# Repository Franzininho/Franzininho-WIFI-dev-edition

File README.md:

# Franzininho WiFi Developer Edition

The **Franzininho WiFi Developer Edition** is a development board designed to evaluate **ESP32-S2 modules** (WROOM and WROVER) and to support the development of the next generation of Franzininho boards.

The Franzininho project was created to help people develop skills in electronics and programming through *DIY* (Do-It-Yourself) activities, aligned with the *maker culture* in Brazil.

As there are still few ESP32-S2-based boards available in the Brazilian market, the Franzininho WiFi was developed to serve as a development platform for this SoC, as well as to help evaluate and validate applications.

---

## Features

### ESP32-S2 Module (WROOM or WROVER)
- Xtensa® LX7 32-bit single-core microprocessor, up to 240 MHz  
- 128 KB ROM  
- 320 KB SRAM  
- 16 KB RTC SRAM  
- 2 MB (8 Mbit) PSRAM (WROVER module only)  
- Wi-Fi 802.11 b/g/n  

### Interfaces
- GPIO, SPI, LCD, UART, I2C, I2S  
- Camera interface  
- IR, pulse counter, LED PWM  
- TWAI (compatible with ISO 11898-1)  
- USB 1.1 OTG  
- ADC, DAC  
- Touch sensor  
- Temperature sensor  

### Hardware
- USB Type-A male connector  
- RGB LED (WS2812) (GPIO 18)  
- 40 pins broken out to 2x20 headers (2.54 mm pitch, 36 GPIOs) — breadboard-friendly  
- Reset and DFU (BOOT0) buttons to enter the ROM bootloader (USB serial, no external adapter required)  
- Serial debug pins (TX and RX) for hardware debug console  
- JTAG pads for advanced debugging access  
- 3.3 V power indicator LED  
- 3.3 V voltage regulator  

### Power Supply
- Micro USB port (default power source)  
- 5 V and GND header pins  
- 3V3 and GND header pins  

### Dimensions
- 72 mm x 30 mm  

### Compatibility
- Compatible with [ESP-IDF](https://docs.espressif.com/projects/esp-idf/en/latest/esp32s2/get-started/index.html)  
- Compatible with [CircuitPython](https://circuitpython.org/)  

---

## License

This project is open-source hardware and is released under the **CERN Open Hardware License**.

The Franzininho WiFi board is certified by OSHWA:  
[UID BR000006](https://certification.oshwa.org/br000006.html)

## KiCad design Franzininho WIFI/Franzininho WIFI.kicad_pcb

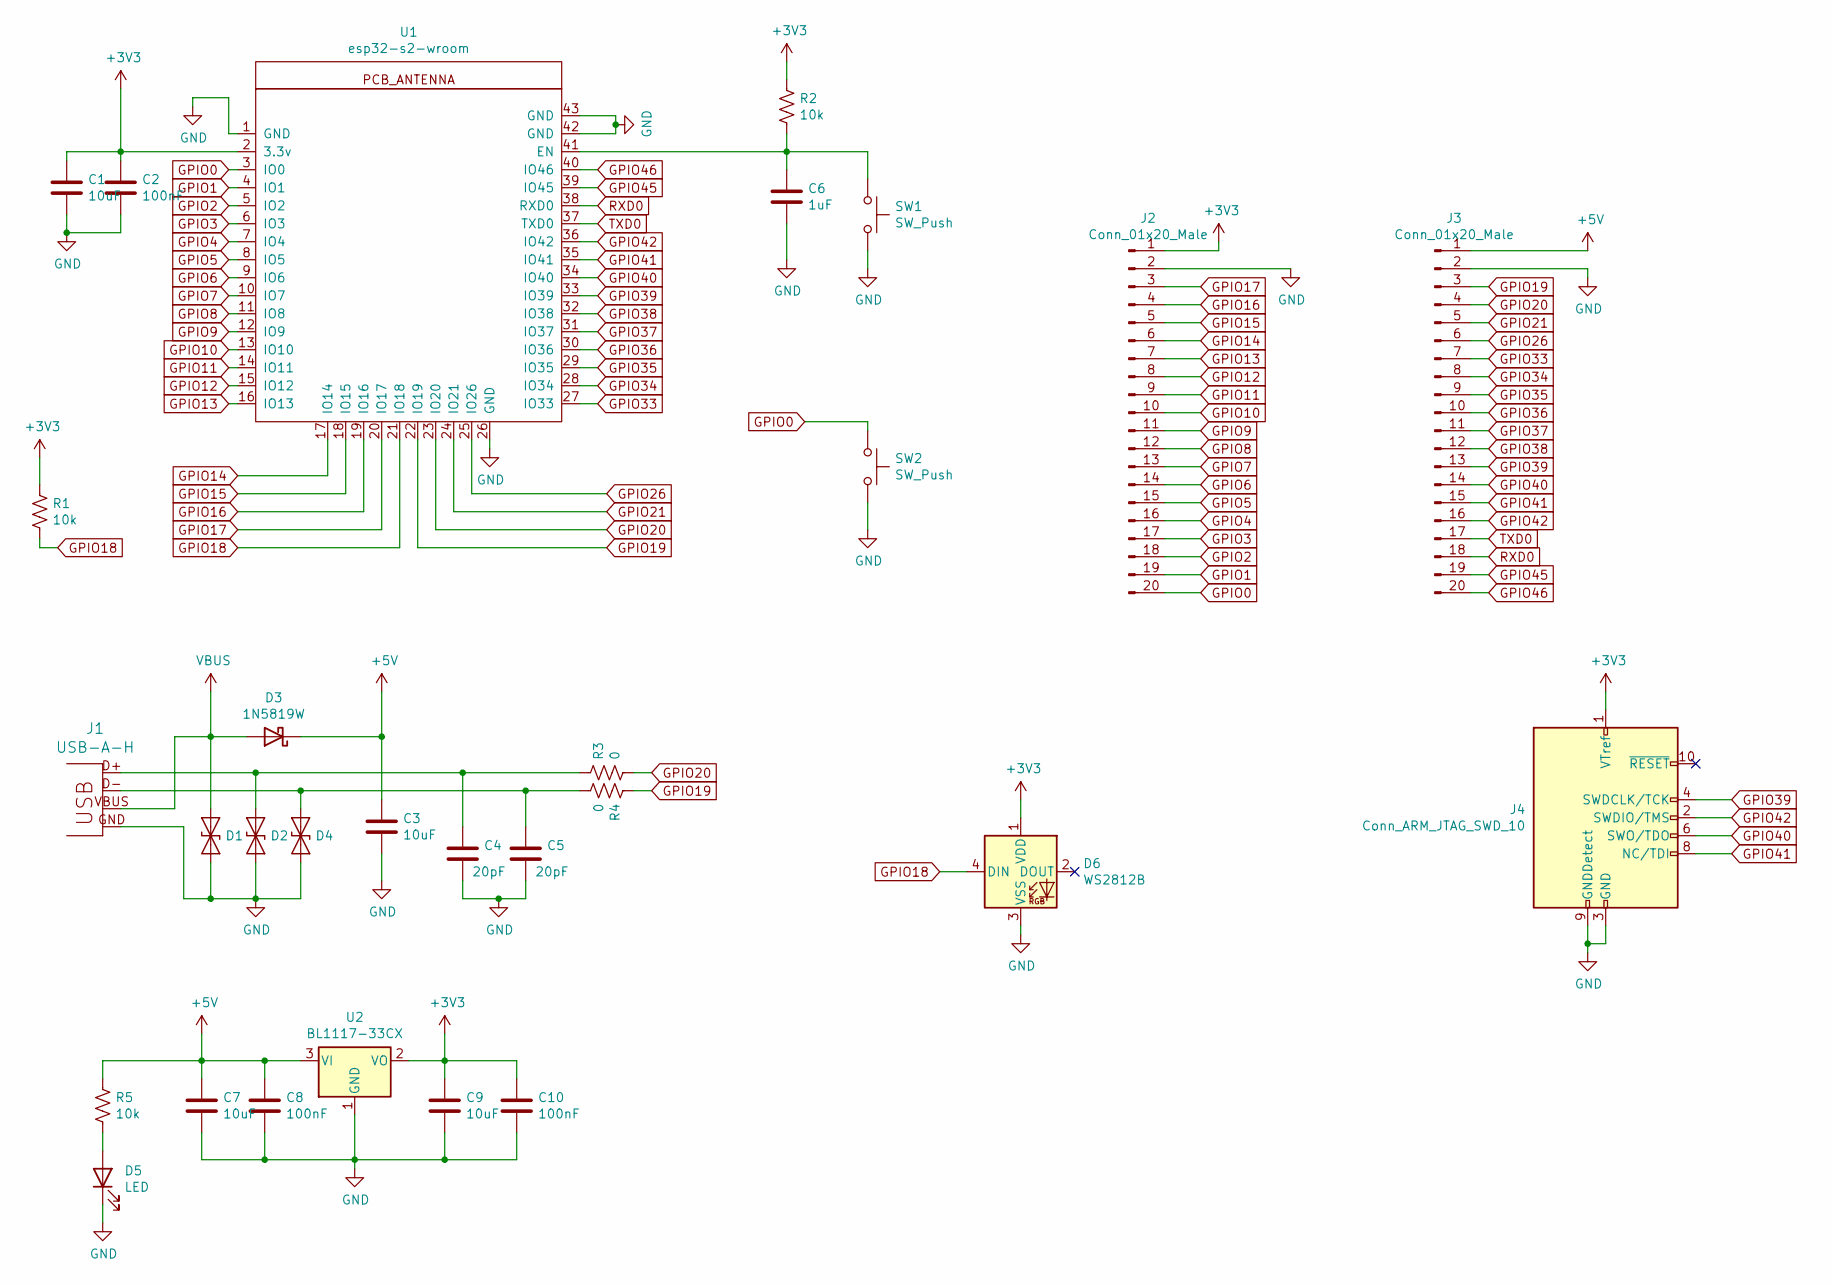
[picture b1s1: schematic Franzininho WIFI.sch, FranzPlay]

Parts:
C1, C3, C7, C9: 10uF; C_0603_1608Metric; LCSC C19702
C2, C8, C10: 100nF; C_0603_1608Metric; LCSC C14663
C4, C5: 20pF; C_0603_1608Metric; LCSC C1648
C6: 1uF; C_0603_1608Metric; LCSC C15849
D1, D2, D4: LESD5D5.0CT1G; D_SOD-523; LCSC C136171
D3: 1N5819W; D_SOD-123F; LCSC C169540
D5: LED; LED_0603_1608Metric; LCSC C2289
D6: WS2812B; LED_WS2812B_PLCC4_5.0x5.0mm_P3.2mm; LCSC C114586
J1: USB-A-H
J2, J3: Conn_01x20_Male; PinSocket_1x20_P2.54mm_Vertical
J4: Conn_ARM_JTAG_SWD_10; PinHeader_2x05_P1.27mm_Vertical_SMD
R1, R2, R5: 10k; R_0603_1608Metric; LCSC C25804
R3, R4: 0; R_0603_1608Metric; LCSC C21189
SW1, SW2: SW_Push; SW_SPST_B3U-1000P
U1: esp32-s2-wroom; esp32-s2-wrooom
U2: BL1117-33CX; SOT-223-3_TabPin2; LCSC C5400

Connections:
+3V3: C1.1, C2.1, C9.1, C10.1, D6.1 (VDD), J2.1, J4.1 (VTref), R1.1, R2.1, U1.2 (3.3v), U2.2 (VO)
+5V: C3.1, C7.1, C8.1, D3.1 (K), J3.1, R5.1, U2.3 (VI)
GND: C1.2, C2.2, C3.2, C4.2, C5.2, C6.2, C7.2, C8.2, C9.2, C10.2, D1.2 (A2), D2.2 (A2), D4.2 (A2), D5.1 (K), D6.3 (VSS), J1.GND, J2.2, J3.2, J4.3 (GND), J4.5 (GND), J4.9 (GNDDetect), SW1.2, SW2.2, U1.1 (GND), U1.26 (GND), U1.42 (GND), U1.43 (GND), U2.1 (GND)
GPIO0: J2.20, SW2.1, U1.3 (IO0)
GPIO1: J2.19, U1.4 (IO1)
GPIO2: J2.18, U1.5 (IO2)
GPIO3: J2.17, U1.6 (IO3)
GPIO4: J2.16, U1.7 (IO4)
GPIO5: J2.15, U1.8 (IO5)
GPIO6: J2.14, U1.9 (IO6)
GPIO7: J2.13, U1.10 (IO7)
GPIO8: J2.12, U1.11 (IO8)
GPIO9: J2.11, U1.12 (IO9)
GPIO10: J2.10, U1.13 (IO10)
GPIO11: J2.9, U1.14 (IO11)
GPIO12: J2.8, U1.15 (IO12)
GPIO13: J2.7, U1.16 (IO13)
GPIO14: J2.6, U1.17 (IO14)
GPIO15: J2.5, U1.18 (IO15)
GPIO16: J2.4, U1.19 (IO16)
GPIO17: J2.3, U1.20 (IO17)
GPIO18: D6.4 (DIN), R1.2, U1.21 (IO18)
GPIO19: J3.3, R4.1, U1.22 (IO19)
GPIO20: J3.4, R3.2, U1.23 (IO20)
GPIO21: J3.5, U1.24 (IO21)
GPIO26: J3.6, U1.25 (IO26)
GPIO33: J3.7, U1.27 (IO33)
GPIO34: J3.8, U1.28 (IO34)
GPIO35: J3.9, U1.29 (IO35)
GPIO36: J3.10, U1.30 (IO36)
GPIO37: J3.11, U1.31 (IO37)
GPIO38: J3.12, U1.32 (IO38)
GPIO39: J3.13, J4.4 (SWDCLK/TCK), U1.33 (IO39)
GPIO40: J3.14, J4.6 (SWO/TDO), U1.34 (IO40)
GPIO41: J3.15, J4.8 (NC/TDI), U1.35 (IO41)
GPIO42: J3.16, J4.2 (SWDIO/TMS), U1.36 (IO42)
GPIO45: J3.19, U1.39 (IO45)
GPIO46: J3.20, U1.40 (IO46)
unnamed: C4.1, D2.1 (A1), J1.D+, R3.1
unnamed: C5.1, D4.1 (A1), J1.D-, R4.2
unnamed: C6.1, R2.2, SW1.1, U1.41 (EN)
unnamed: D5.2 (A), R5.2
RXD0: J3.18, U1.38 (RXD0)
TXD0: J3.17, U1.37 (TXD0)
VBUS: D1.1 (A1), D3.2 (A), J1.VBUS

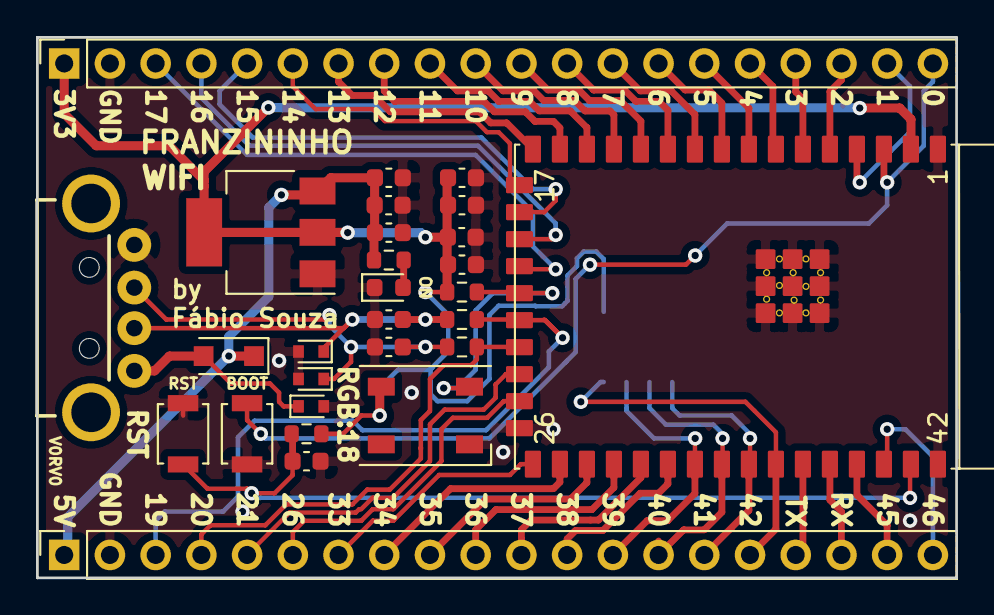
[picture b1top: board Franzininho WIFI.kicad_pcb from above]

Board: 2 copper layers, 51.1 x 30.0 mm, 29 parts (0 on the bottom side), 45 nets.

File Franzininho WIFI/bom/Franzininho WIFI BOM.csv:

Reference, Value, Footprint, Datasheet, LCSC, PN
"U1","esp32-s2-wroom","esp32-s2:esp32-s2-wrooom",""
"D1","LESD5D5.0CT1G","Diode_SMD:D_SOD-523","https://datasheet.lcsc.com/szlcsc/Leshan-Radio-LESD5Z5-0T1G_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","C136171","LESD5Z5.0T1G"
"D2","LESD5D5.0CT1G","Diode_SMD:D_SOD-523","https://datasheet.lcsc.com/szlcsc/Leshan-Radio-LESD5Z5-0T1G_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","C136171","LESD5Z5.0T1G"
"D4","LESD5D5.0CT1G","Diode_SMD:D_SOD-523","https://datasheet.lcsc.com/szlcsc/Leshan-Radio-LESD5Z5-0T1G_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","C136171","LESD5Z5.0T1G"
"D3","1N5819W","Diode_SMD:D_SOD-123F","Shandong-Jingdao-Microelectronics-1N5819W_C169540.pdf","C169540","1N5819W"
"C3","10uF","Capacitor_SMD:C_0603_1608Metric","Samsung-Electro-Mechanics-CL10A106KP8NNNC_C19702.pdf","C19702","CL10A106KP8NNNC"
"C4","20pF","Capacitor_SMD:C_0603_1608Metric","https://datasheet.lcsc.com/szlcsc/Samsung-Electro-Mechanics-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","C1648","CL10C200JB8NNNC"
"R1","10k","Resistor_SMD:R_0603_1608Metric","~","C25804","0603WAF1002T5E"
"R2","10k","Resistor_SMD:R_0603_1608Metric","~","C25804","0603WAF1002T5E"
"C6","1uF","Capacitor_SMD:C_0603_1608Metric","https://datasheet.lcsc.com/szlcsc/Samsung-Electro-Mechanics-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","C15849","CL10A105KB8NNNC"
"C2","100nF","Capacitor_SMD:C_0603_1608Metric","https://datasheet.lcsc.com/szlcsc/YAGEO-CC0603KRX7R9BB104_C1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","C14663","CC0603KRX7R9BB104"
"C5","20pF","Capacitor_SMD:C_0603_1608Metric","https://datasheet.lcsc.com/szlcsc/Samsung-Electro-Mechanics-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","C1648","CL10C200JB8NNNC"
"C1","10uF","Capacitor_SMD:C_0603_1608Metric","Samsung-Electro-Mechanics-CL10A106KP8NNNC_C19702.pdf","C19702","CL10A106KP8NNNC"
"J1","USB-A-H","LIBS:USB-A-H",""
"R3","0","Resistor_SMD:R_0603_1608Metric","~","C21189","0603WAF0000T5E"
"R4","0","Resistor_SMD:R_0603_1608Metric","~","C21189","0603WAF0000T5E"
"U2","BL1117-33CX","Package_TO_SOT_SMD:SOT-223-3_TabPin2","https://datasheet.lcsc.com/szlcsc/Shanghai-Belling-BL1117-33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","C5400","BL1117-33CX"
"C7","10uF","Capacitor_SMD:C_0603_1608Metric","Samsung-Electro-Mechanics-CL10A106KP8NNNC_C19702.pdf","C19702","CL10A106KP8NNNC"
"C8","100nF","Capacitor_SMD:C_0603_1608Metric","https://datasheet.lcsc.com/szlcsc/YAGEO-CC0603KRX7R9BB104_C1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","C14663","CC0603KRX7R9BB104"
"C9","10uF","Capacitor_SMD:C_0603_1608Metric","Samsung-Electro-Mechanics-CL10A106KP8NNNC_C19702.pdf","C19702","CL10A106KP8NNNC"
"C10","100nF","Capacitor_SMD:C_0603_1608Metric","https://datasheet.lcsc.com/szlcsc/YAGEO-CC0603KRX7R9BB104_C1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","C14663","CC0603KRX7R9BB104"
"J2","Conn_01x20_Male","Connector_PinSocket_2.54mm:PinSocket_1x20_P2.54mm_Vertical","~"
"J3","Conn_01x20_Male","Connector_PinSocket_2.54mm:PinSocket_1x20_P2.54mm_Vertical","~"
"D5","LED","LED_SMD:LED_0603_1608Metric","https://datasheet.lcsc.com/szlcsc/Hubei-KENTO-Elec-XL-0603QY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","C2289","XL-0603QYGC"
"R5","10k","Resistor_SMD:R_0603_1608Metric","~","C25804","0603WAF1002T5E"
"SW1","SW_Push","Button_Switch_SMD:SW_SPST_B3U-1000P","~"
"SW2","SW_Push","Button_Switch_SMD:SW_SPST_B3U-1000P","~"
"D6","WS2812B","LED_SMD:LED_WS2812B_PLCC4_5.0x5.0mm_P3.2mm","https://datasheet.lcsc.com/szlcsc/Worldsemi-WS2812B-B_C114586.pdf","C114586","WS2812B-B"
"J4","Conn_ARM_JTAG_SWD_10","Connector_PinHeader_1.27mm:PinHeader_2x05_P1.27mm_Vertical_SMD","http://infocenter.arm.com/help/topic/com.arm.doc.ddi0314h/DD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"

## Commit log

2020-12-02 Adicionando licença CERN
2020-12-02 Adicionando imagens da placa
2020-12-22 Adicionando InteractiveHtmlBom para visualização dos componentes na montagem
2021-03-13 organização da licença em uma pasta
2021-03-20 Adicionando iamgens e organizando as pastas
2021-03-24 Ajustando plnailha BOM
2021-04-22 arrumei a imagem do oshwa
    Ele não estava carregando por faltar o " license/ " antes do node da imagem.
2021-04-22 Ajuste de tradução de License para Licença
2021-06-01 Adicionando arquivo de posicionamento dos componentes
2022-04-12 Atualizando o nome para developer edition
2026-03-24 Create README_PTBR.md for Franzininho WiFi
    Add README for Franzininho WiFi project with details on features, hardware, and compatibility.
2026-03-24 Revise README for Franzininho WiFi Developer Edition
    Updated the README to improve clarity and organization of information regarding the Franzininho WiFi Developer Edition, including features, specifications, and licensing.
